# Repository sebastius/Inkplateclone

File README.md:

# Inkplateclone
A clone of the Inkplate schematic in Kicad. Not to steal, but to have a base schematic i can improve upon.

Based on https://github.com/e-radionicacom/Inkplate-6-hardware

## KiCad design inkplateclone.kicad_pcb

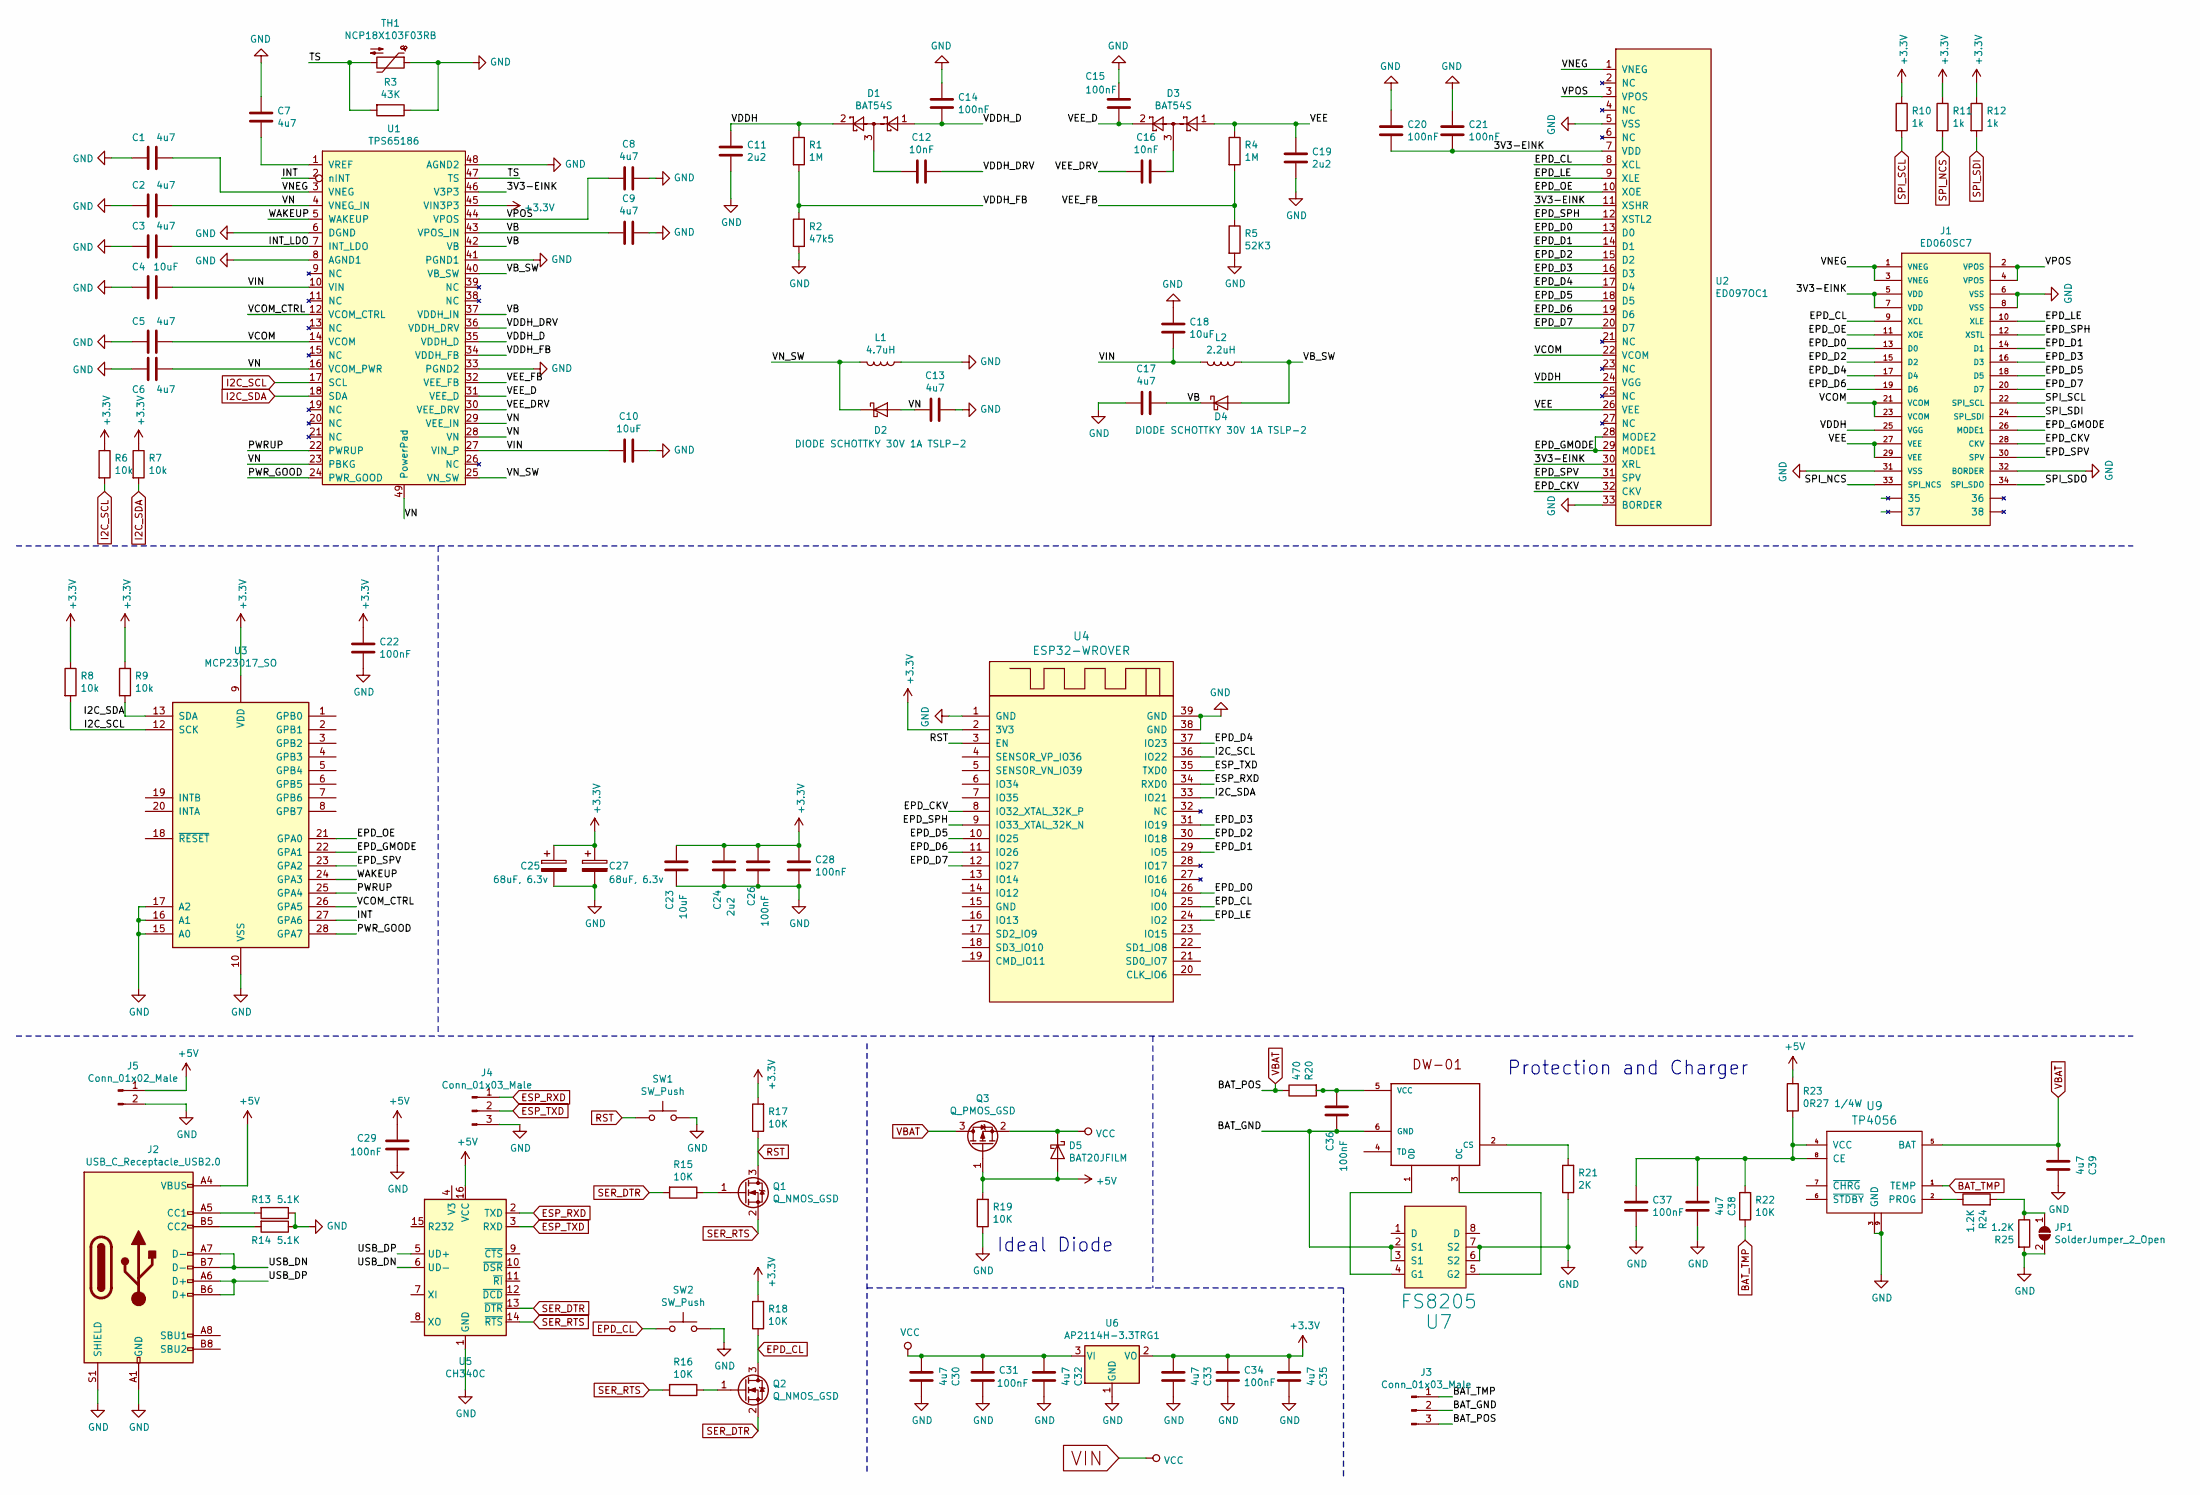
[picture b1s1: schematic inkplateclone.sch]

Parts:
C1, C2, C3, C5, C6, C7, C8, C9, C13, C17, C30, C32, C33, C35, C38, C39: 4u7; C_0805_2012Metric
C4, C10, C18, C23: 10uF; C_1206_3216Metric
C11, C19, C24: 2u2; C_0805_2012Metric
C12, C16: 10nF; C_0805_2012Metric
C14, C15, C20, C21, C22, C26, C28, C29, C31, C34, C36, C37: 100nF; C_0805_2012Metric
C25, C27: 68uF, 6.3v; CP_EIA-3528-15_AVX-H_Pad1.50x2.35mm_HandSolder
D1, D3: BAT54S; SOT-23
D2, D4: DIODE SCHOTTKY 30V 1A TSLP-2; D_SOD-323
D5: BAT20JFILM; D_SOD-323
J1: ED060SC7; PANASONIC_AXT334124
J2: USB_C_Receptacle_USB2.0; USB_C_Receptacle_HRO_TYPE-C-31-M-12
J3: Conn_01x03_Male; JST_PH_S3B-PH-SM4-TB_1x03-1MP_P2.00mm_Horizontal
J4: Conn_01x03_Male; PinHeader_1x03_P2.54mm_Vertical
J5: Conn_01x02_Male; PinHeader_1x02_P2.54mm_Vertical
JP1: SolderJumper_2_Open; SolderJumper-2_P1.3mm_Open_Pad1.0x1.5mm
L1: 4.7uH; L_Coilcraft_XxL4040
L2: 2.2uH; L_Coilcraft_XxL4040
Q1, Q2: Q_NMOS_GSD; SOT-23
Q3: Q_PMOS_GSD; SOT-23
R1, R4: 1M; R_0805_2012Metric
R2: 47k5; R_0805_2012Metric
R3: 43K; R_0805_2012Metric
R5: 52K3; R_0805_2012Metric
R6, R7, R8, R9: 10k; R_0805_2012Metric
R10, R11, R12: 1k; R_0805_2012Metric
R13, R14: 5.1K; R_0805_2012Metric
R15, R16, R17, R18, R19, R22: 10K; R_0805_2012Metric
R20: 470; R_0805_2012Metric
R21: 2K; R_0805_2012Metric
R23: 0R27 1/4W; R_1206_3216Metric
R24, R25: 1.2K; R_0805_2012Metric
SW1, SW2: SW_Push; SW_Push_1P1T_NO_6x6mm_H9.5mm
TH1: NCP18X103F03RB; R_0805_2012Metric
U1: TPS65186; QFN-48-1EP_7x7mm_P0.5mm_EP5.3x5.3mm_ThermalVias
U2: ED097OC1; Hirose_FH12-33S-0.5SH_1x33-1MP_P0.50mm_Horizontal
U3: MCP23017_SO; SOIC-28W_7.5x17.9mm_P1.27mm
U4: ESP32-WROVER
U5: CH340C; SOIC-16_3.9x9.9mm_P1.27mm
U6: AP2114H-3.3TRG1; SOT-223-3_TabPin2
U7: FS8205; TSSOP-8_4.4x3mm_P0.65mm
U8: DW-01; SOT-23-6
U9: TP4056; SOIC-8-1EP_3.9x4.9mm_P1.27mm_EP2.29x3mm

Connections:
+3V3: C22.2, C23.2, C24.2, C25.1, C26.2, C27.1, C28.2, C33.2, C34.2, C35.2, R6.1, R7.1, R8.1, R9.1, R10.1, R11.1, R12.1, R17.2, R18.2, U1.45 (VIN3P3), U3.9 (VDD), U4.2 (3V3), U6.2 (VO)
+5V: C29.2, D5.2 (A), J2.A4 (VBUS), J2.A9 (VBUS), J2.B4 (VBUS), J2.B9 (VBUS), J5.1, Q3.1 (G), R19.2, R23.1, U5.16 (VCC)
/3V3-EINK: C20.1, C21.1, J1.5 (VDD), J1.7 (VDD), U1.46 (V3P3), U2.7 (VDD), U2.11 (XSHR), U2.30 (XRL)
/BAT_GND: C36.1, J3.2, U7.2 (S1), U7.3 (S1), U8.6 (GND)
/EPD_CKV: J1.28 (CKV), U2.32 (CKV), U4.8 (IO32_XTAL_32K_P)
/EPD_D0: J1.13 (D0), U2.13 (D0), U4.26 (IO4)
/EPD_D1: J1.14 (D1), U2.14 (D1), U4.29 (IO5)
/EPD_D2: J1.15 (D2), U2.15 (D2), U4.30 (IO18)
/EPD_D3: J1.16 (D3), U2.16 (D3), U4.31 (IO19)
/EPD_D4: J1.17 (D4), U2.17 (D4), U4.37 (IO23)
/EPD_D5: J1.18 (D5), U2.18 (D5), U4.10 (IO25)
/EPD_D6: J1.19 (D6), U2.19 (D6), U4.11 (IO26)
/EPD_D7: J1.20 (D7), U2.20 (D7), U4.12 (IO27)
/EPD_GMODE: J1.26 (MODE1), U2.28 (MODE2), U2.29 (MODE1), U3.22 (GPA1)
/EPD_LE: J1.10 (XLE), U2.9 (XLE), U4.24 (IO2)
/EPD_OE: J1.11 (XOE), U2.10 (XOE), U3.21 (GPA0)
/EPD_SPH: J1.12 (XSTL), U2.12 (XSTL2), U4.9 (IO33_XTAL_32K_N)
/EPD_SPV: J1.30 (SPV), U2.31 (SPV), U3.23 (GPA2)
/INT: U1.2 (nINT), U3.27 (GPA6)
/INT_LDO: C3.1, U1.7 (INT_LDO)
/PWRUP: U1.22 (PWRUP), U3.25 (GPA4)
/PWR_GOOD: U1.24 (PWR_GOOD), U3.28 (GPA7)
/SPI_SDO: J1.34 (SPI_SDO)
/TS: R3.2, TH1.2, U1.47 (TS)
/USB_DN: J2.A7 (D-), J2.B7 (D-), U5.6 (UD-)
/USB_DP: J2.A6 (D+), J2.B6 (D+), U5.5 (UD+)
/VB: C9.2, C17.1, D4.1 (K), U1.37 (VDDH_IN), U1.42 (VB), U1.43 (VPOS_IN)
/VB_SW: D4.2 (A), L2.1, U1.40 (VB_SW)
/VCOM: C5.1, J1.21 (VCOM), J1.23 (VCOM), U1.14 (VCOM), U2.22 (VCOM)
/VCOM_CTRL: U1.12 (VCOM_CTRL), U3.26 (GPA5)
/VDDH: C11.2, D1.2, J1.25 (VGG), R1.1, U2.24 (VGG)
/VDDH_D: C14.1, D1.1, U1.35 (VDDH_D)
/VDDH_DRV: C12.2, U1.36 (VDDH_DRV)
/VDDH_FB: R1.2, R2.1, U1.34 (VDDH_FB)
/VEE: C19.2, D3.1, J1.27 (VEE), J1.29 (VEE), R4.1, U2.26 (VEE)
/VEE_D: C15.1, D3.2, U1.31 (VEE_D)
/VEE_DRV: C16.1, U1.30 (VEE_DRV)
/VEE_FB: R4.2, R5.1, U1.32 (VEE_FB)
/VN: C2.1, C6.1, C13.2, D2.2 (A), U1.4 (VNEG_IN), U1.16 (VCOM_PWR), U1.23 (PBKG), U1.28 (VN), U1.29 (VEE_IN), U1.49 (PowerPad)
/VNEG: C1.1, J1.1 (VNEG), J1.3 (VNEG), U1.3 (VNEG), U2.1 (VNEG)
/VN_SW: D2.1 (K), L1.2, U1.25 (VN_SW)
/VPOS: C8.2, J1.2 (VPOS), J1.4 (VPOS), U1.44 (VPOS), U2.3 (VPOS)
/WAKEUP: U1.5 (WAKEUP), U3.24 (GPA3)
BAT_TMP: J3.1, R22.1, U9.1 (TEMP)
EPD_CL: J1.9 (XCL), Q2.3 (D), R18.1, SW2.1, U2.8 (XCL), U4.25 (IO0)
ESP_RXD: J4.1, U4.34 (RXD0), U5.2 (TXD)
ESP_TXD: J4.2, U4.35 (TXD0), U5.3 (RXD)
GND: C1.2, C2.2, C3.2, C4.2, C5.2, C6.2, C7.1, C8.1, C9.1, C10.1, C11.1, C13.1, C14.2, C15.2, C17.2, C18.2, C19.1, C20.2, C21.2, C22.1, C23.1, C24.1, C25.2, C26.1, C27.2, C28.1, C29.1, C30.1, C31.1, C32.1, C33.1, C34.1, C35.1, C37.1, C38.1, C39.1, J1.6 (VSS), J1.8 (VSS), J1.31 (VSS), J1.32 (BORDER), J2.A1 (GND), J2.A12 (GND), J2.B1 (GND), J2.B12 (GND), J2.S1 (SHIELD), J4.3, J5.2, JP1.2 (B), L1.1, R2.2, R3.1, R5.2, R13.1, R14.1, R19.1, R21.1, R25.2, SW1.2, SW2.2, TH1.1, U1.6 (DGND), U1.8 (AGND1), U1.33 (PGND2), U1.41 (PGND1), U1.48 (AGND2), U2.5 (VSS), U2.33 (BORDER), U3.10 (VSS), U3.15 (A0), U3.16 (A1), U3.17 (A2), U4.1 (GND), U4.38 (GND), U4.39 (GND), U5.1 (GND), U6.1 (GND), U7.6 (S2), U7.7 (S2), U9.3 (GND), U9.9
I2C_SCL: R6.2, R8.2, U1.17 (SCL), U3.12 (SCK), U4.36 (IO22)
I2C_SDA: R7.2, R9.2, U1.18 (SDA), U3.13 (SDA), U4.33 (IO21)
unnamed: C7.2, U1.1 (VREF)
unnamed: C12.1, D1.3
unnamed: C16.2, D3.3
unnamed: C36.2, R20.2, U8.5 (VCC)
unnamed: C37.2, C38.2, R22.2, R23.2, U9.4 (VCC), U9.8 (CE)
unnamed: J2.A5 (CC1), R13.2
unnamed: J2.B5 (CC2), R14.2
unnamed: JP1.1 (A), R24.2, R25.1
unnamed: Q1.1 (G), R15.1
unnamed: Q2.1 (G), R16.1
unnamed: R21.2, U8.2 (CS)
unnamed: R24.1, U9.2 (PROG)
unnamed: U7.4 (G1), U8.1 (OD)
unnamed: U7.5 (G2), U8.3 (OC)
RST: Q1.3 (D), R17.1, SW1.1, U4.3 (EN)
SER_DTR: Q2.2 (S), R15.2, U5.13 (~DTR)
SER_RTS: Q1.2 (S), R16.2, U5.14 (~RTS)
SPI_NCS: J1.33 (SPI_NCS), R11.2
SPI_SCL: J1.22 (SPI_SCL), R10.2
SPI_SDI: J1.24 (SPI_SDI), R12.2
VBAT: C39.2, J3.3, Q3.3 (D), R20.1, U9.5 (BAT)
VIN: C4.1, C10.2, C18.1, C30.2, C31.2, C32.2, D5.1 (K), L2.2, Q3.2 (S), U1.10 (VIN), U1.27 (VIN_P), U6.3 (VI)

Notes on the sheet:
Ideal Diode
Protection and Charger

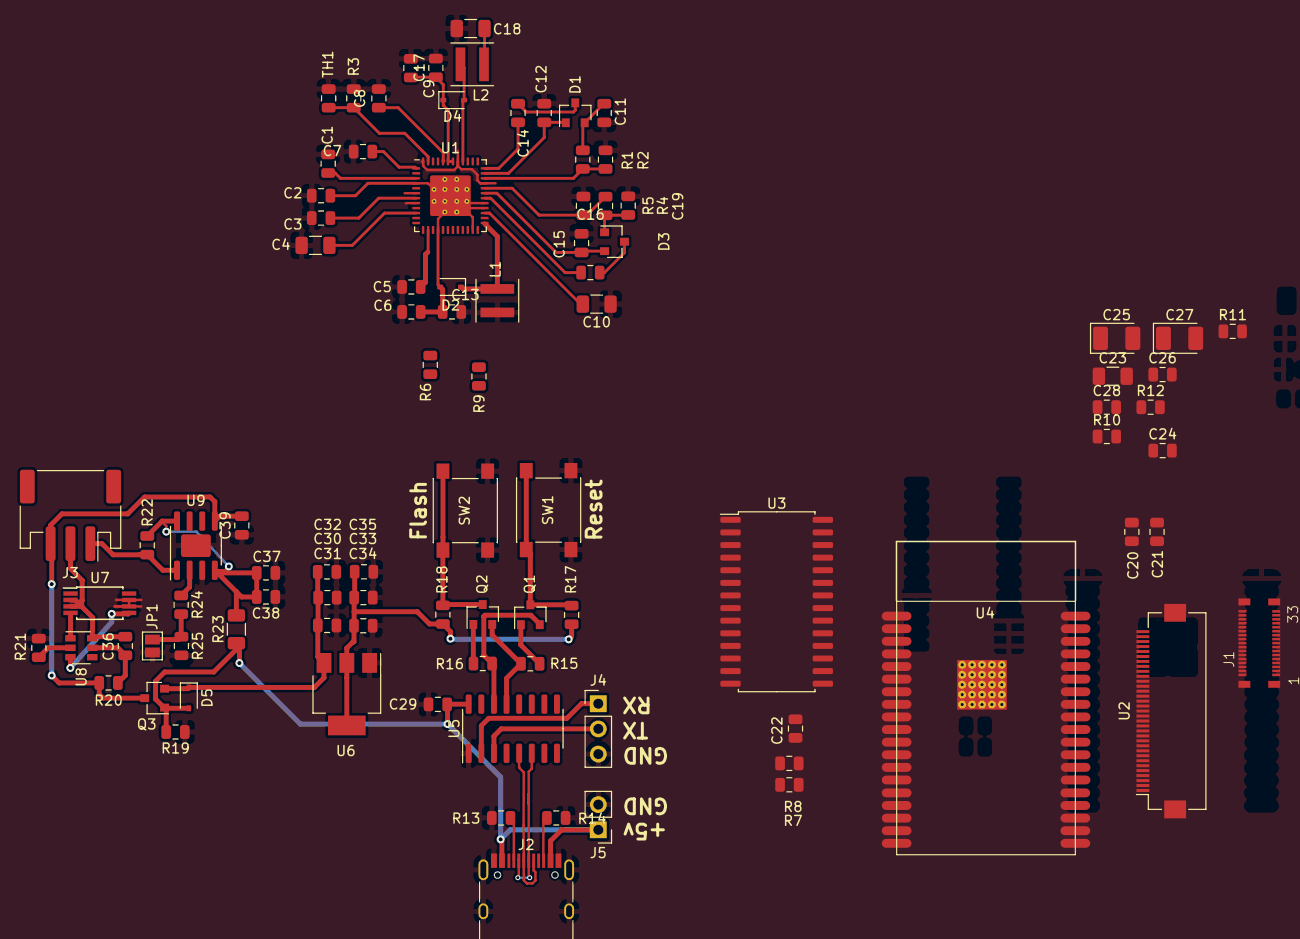
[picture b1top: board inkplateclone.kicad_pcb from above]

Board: 2 copper layers, 92 parts (0 on the bottom side), 71 nets.

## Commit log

2020-05-05 ED060SC7 as a symbol now
2020-05-05 datasheet ed097oc1 added
2020-05-05 datasheet tps65186 added
2020-05-05 repo cleanup and structuring of folders
2020-05-05 gitignore
2020-05-05 cleanup schematic, early pcb work for the 6 inch connector
2020-05-05 removed some backups
2020-05-05 added SPI pullup resistors for the 6inch display
2020-05-05 wiring up the Wrover, WIP
2020-05-05 ripped up and made a mess but its cool. Also added cooling pad underneath TPS56186 chip
2020-05-09 added usb C-serial and fixed errors in the tps65186 part of the schematic
2020-05-09 added ideal diode and 3.3v circuit. Battery stuff and inputs still todo
2020-05-10 added charger and protection, need to verify.
2020-05-10 done some ratsnests
2020-05-10 more ratsnest, push before sleep
2020-05-10 removed polyfuses, fixes #2
2020-05-10 replaced LDO, fixes #1
2020-05-10 routed the usb c serial connection and went to town with alignment
2020-05-10 added some 3d models, much prettier.
2020-05-11 routed switches and added 3d models
2020-05-11 routed charger and ideal diode
2020-05-11 routed voltage regulator
2020-05-11 added 3d model for battery connector
2020-05-11 cleaned up silkscreen
2020-05-11 added 3d models for the connectors. Not satisfied but they will do for now.
2020-05-12 bedtijd
2020-05-12 opruimen
